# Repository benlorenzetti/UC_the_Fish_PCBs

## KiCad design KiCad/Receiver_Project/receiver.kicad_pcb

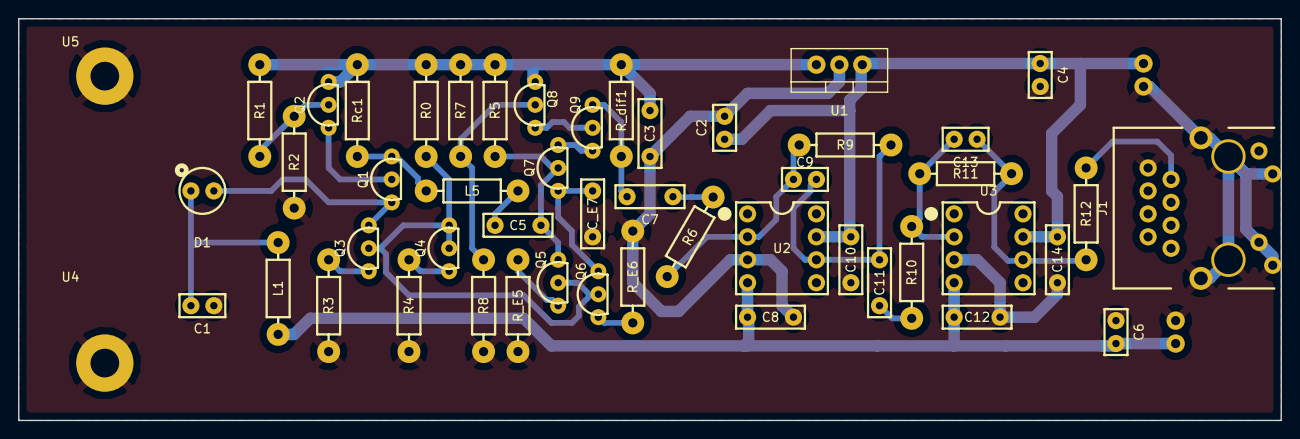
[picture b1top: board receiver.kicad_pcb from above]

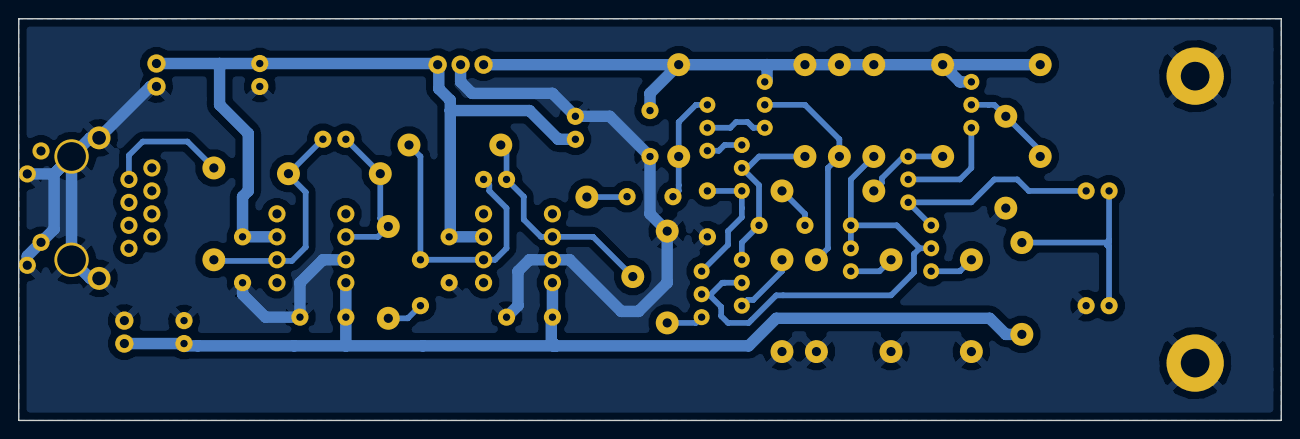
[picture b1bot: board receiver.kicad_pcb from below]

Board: 2 copper layers, 139.7 x 44.5 mm, 52 parts (2 on the bottom side), 28 nets.

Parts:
BT1, BT2: 9V; point1_pitch_Header
C1: 47 uF; 100Mil_Passive
C2: 0.33uF; 100Mil_Passive
C3: 0.1uF; 200Mil_Passive
C4, C6: 47uF; 100Mil_Passive
C5: 100nF; 200Mil_Passive
C7, C11: 330nF; 200Mil_Passive
C8, C10, C12, C14: 0.1u; 200Mil_Passive
C9, C13: 2pF; 100Mil_Passive
C_E7: 100 uF; 200Mil_Passive
D1: MTD3010PM
J1: RB1-125BAG1A
L1: 10 uH; 400Mil_Passive
L5: 0.1 uH; 400Mil_Passive
Q1, Q7, Q9: PN2369A; TO-92
Q2, Q3, Q4, Q5, Q6, Q8: 2N3904; TO-92
R0: 1.7k; 400Mil_Passive
R1: 723; 400Mil_Passive
R2: 884; 400Mil_Passive
R3: 10.6; 400Mil_Passive
R4: 106; 400Mil_Passive
R5: 2.7k; 400Mil_Passive
R6, R10, R12: 100; 400Mil_Passive
R7: 667; 400Mil_Passive
R8: 2k; 400Mil_Passive
R9, R11: 1k; 400Mil_Passive
R_E5: 342; 400Mil_Passive
R_E6: 25; 400Mil_Passive
R_dif1: 100; 400Mil_Passive
Rc1: 100; 400Mil_Passive
U1: MC7805CTG; TO-220
U2, U3: LM7171; 8_Pin_Socket
U4, U5: Physical_Mount; Mounting_Via

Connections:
+5V: C3.1, Q2.3, Q8.3, R0.1, R1.1, R5.1, R7.1, R_dif1.1, Rc1.1, U1.3
+9V: BT1.1, C2.1, C4.1, C10.2, C14.2, U1.1, U2.7, U3.7
-9V: BT2.2, C6.2, C8.1, C12.1, L1.1, U2.4, U3.4
/Stage 1/in: D1.1, Q1.1, Q3.3
/Stage 1/mirror: Q3.2, Q4.2, Q4.3, Q5.2, Q6.2, R0.2
/Stage 2/in2: L5.2, Q1.3, Rc1.2
/Stage 2/out2: C7.2, Q9.3, R_dif1.2
GND: BT1.2, BT2.1, C1.1, C2.2, C3.2, C4.2, C6.1, C8.2, C10.1, C12.2, C14.1, C_E7.2, J1.8, J1.9, R2.2, R3.2, R4.2, R8.2, R_E5.2, R_E6.2, U1.2, U2.3, U3.3, U4.1, U5.1
unnamed: C1.2, D1.2, L1.2
unnamed: C5.1, Q5.3, Q7.2, R5.2
unnamed: C5.2, L5.1
unnamed: C7.1, R6.2
unnamed: C9.2, R6.1, R9.2, U2.2
unnamed: C11.1, R10.2
unnamed: C9.1, C11.2, R9.1, U2.6
unnamed: C13.1, R11.1, R12.2, U3.6
unnamed: C13.2, R10.1, R11.2, U3.2
unnamed: C_E7.1, Q6.3, Q7.1
unnamed: J1.7, R12.1
unnamed: Q1.2, Q2.1
unnamed: Q2.2, R1.2, R2.1
unnamed: Q3.1, R3.1
unnamed: Q4.1, R4.1
unnamed: Q5.1, R_E5.1
unnamed: Q6.1, R_E6.1
unnamed: Q7.3, Q9.1
unnamed: Q8.1, Q9.2
unnamed: Q8.2, R7.2, R8.1

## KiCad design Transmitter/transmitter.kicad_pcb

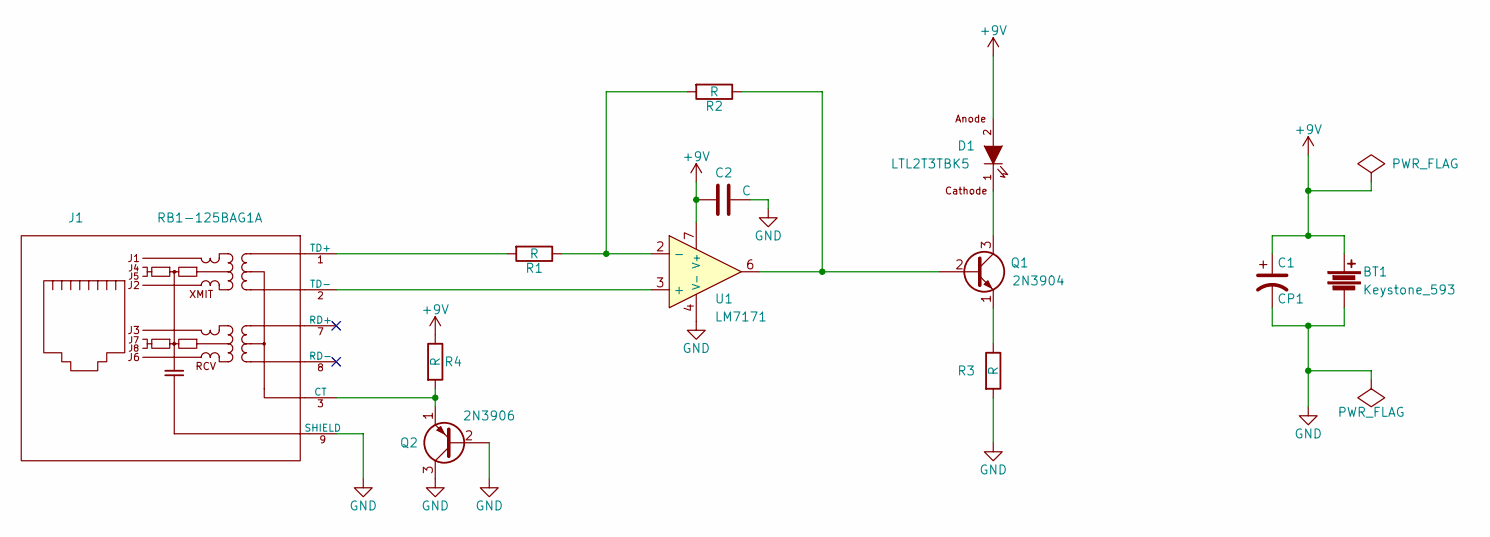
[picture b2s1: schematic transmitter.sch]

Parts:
BT1: Keystone_593; 9V_Contacts
C1: CP1; TAP107K006SCS
C2: C; 200Mil_Passive
D1: LTL2T3TBK5
J1: RB1-125BAG1A
Q1: 2N3904; TO-92
Q2: 2N3906; TO-92
R1, R2, R3, R4: R; 400Mil_Passive
U1: LM7171; 8_Pin_Socket

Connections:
+9V: BT1.1, C1.1, C2.2, D1.2 (A), R4.1, U1.7 (V+)
GND: BT1.2, C1.2, C2.1, J1.9 (SHIELD), Q2.2 (B), Q2.3 (C), R3.2, U1.4 (V-)
unnamed: D1.1 (K), Q1.3 (C)
unnamed: J1.1 (TD+), R1.2
unnamed: J1.2 (TD-), U1.3 (+)
unnamed: J1.3 (CT), Q2.1 (E), R4.2
unnamed: Q1.1 (E), R3.1
unnamed: Q1.2 (B), R2.1, U1.6
unnamed: R1.1, R2.2, U1.2 (-)

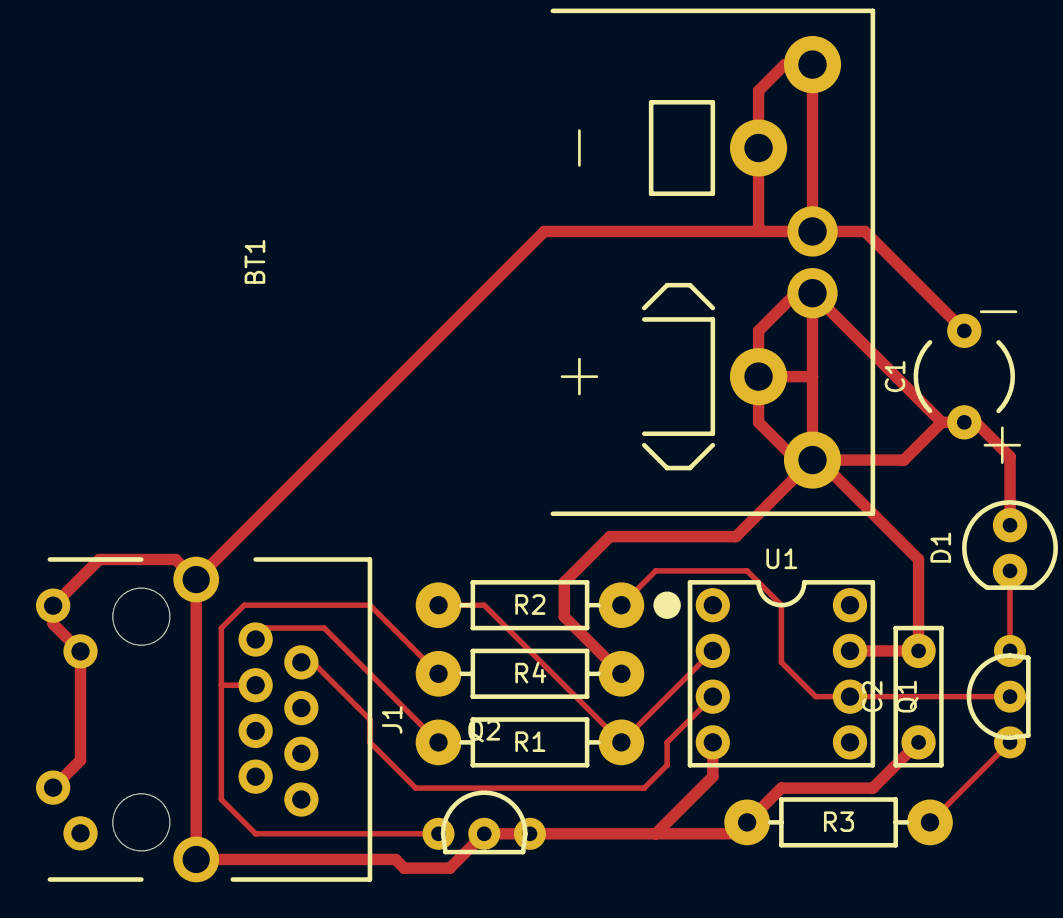
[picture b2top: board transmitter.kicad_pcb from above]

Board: 2 copper layers, 12 parts (0 on the bottom side), 9 nets.

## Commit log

2016-03-26 Part Libraries and Transmitter Circuit Largely Complete
2016-03-29 Transmitter complete and tested, receiver routed
2016-03-31 receiver milled
2016-04-09 added simulation labels to receiver schematic
2017-08-23 synchronize PCs
